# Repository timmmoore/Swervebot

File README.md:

# Swervebot

https://cad.onshape.com/documents/ee819cf6ea491e04f0fba739/w/47ab37900572e080b95199d2/e/a63b98e65827662d9141c87c

https://cad.onshape.com/documents/98357d3c8f8b098add8002f2/w/b5a1efd9deb641ade0f32837/e/772a9ea7ca7ad6a00d48e67d

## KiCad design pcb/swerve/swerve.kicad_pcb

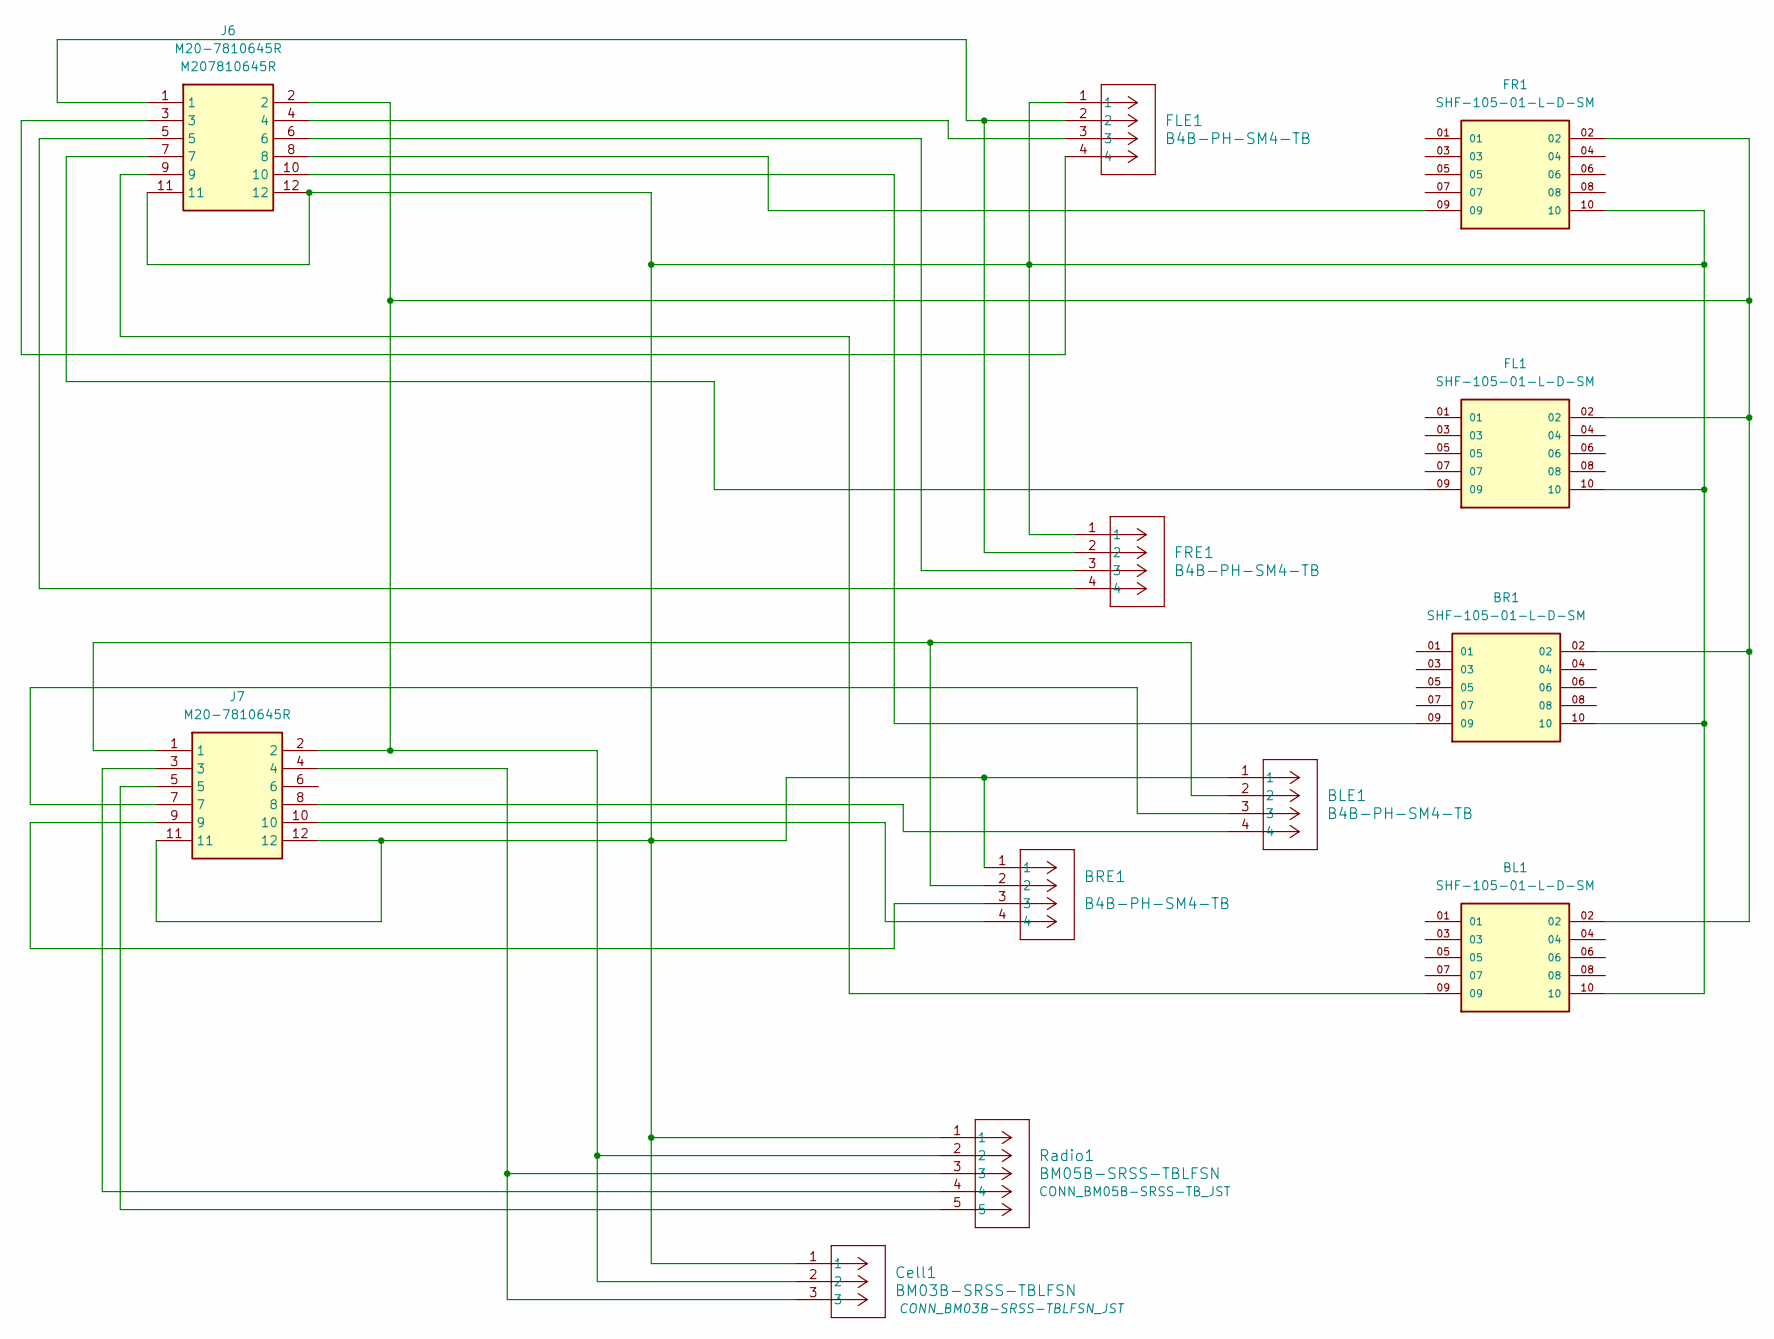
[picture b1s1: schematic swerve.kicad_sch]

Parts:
BL1: SHF-105-01-L-D-SM; SAMTEC_SHF-105-01-L-D-SM; PARTREV A
BLE1: B4B-PH-SM4-TB; JST_PH_B4B-PH-SM4-TB_1x04-1MP_P2.00mm_Vertical
BR1: SHF-105-01-L-D-SM; SAMTEC_SHF-105-01-L-D-SM; PARTREV A
BRE1: B4B-PH-SM4-TB; JST_PH_B4B-PH-SM4-TB_1x04-1MP_P2.00mm_Vertical
Cell1: BM03B-SRSS-TBLFSN; CONN_BM03B-SRSS-TBLFSN_JST
FL1: SHF-105-01-L-D-SM; SAMTEC_SHF-105-01-L-D-SM; PARTREV A
FLE1: B4B-PH-SM4-TB; JST_PH_B4B-PH-SM4-TB_1x04-1MP_P2.00mm_Vertical
FR1: SHF-105-01-L-D-SM; SAMTEC_SHF-105-01-L-D-SM; PARTREV A
FRE1: B4B-PH-SM4-TB; JST_PH_B4B-PH-SM4-TB_1x04-1MP_P2.00mm_Vertical
J6, J7: M20-7810645R; M207810645R; Manufacturer_Part_Number M20-7810645R; Mouser Part Number 855-M20-7810645R
Radio1: BM05B-SRSS-TBLFSN; CONN_BM05B-SRSS-TB_JST

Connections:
unnamed: BL1.02, BR1.02, Cell1.2, FL1.02, FR1.02, J6.2, J7.2, Radio1.2
unnamed: BL1.09, J6.9
unnamed: BL1.10, BLE1.1, BR1.10, BRE1.1, Cell1.1, FL1.10, FLE1.1, FR1.10, FRE1.1, J6.11, J6.12, J7.11, J7.12, Radio1.1
unnamed: BLE1.2, BRE1.2, J7.1
unnamed: BLE1.3, J7.7
unnamed: BLE1.4, J7.8
unnamed: BR1.09, J6.10
unnamed: BRE1.3, J7.9
unnamed: BRE1.4, J7.10
unnamed: Cell1.3, J7.4, Radio1.3
unnamed: FL1.09, J6.7
unnamed: FLE1.2, FRE1.2, J6.1
unnamed: FLE1.3, J6.4
unnamed: FLE1.4, J6.3
unnamed: FR1.09, J6.8
unnamed: FRE1.3, J6.6
unnamed: FRE1.4, J6.5
unnamed: J7.3, Radio1.4
unnamed: J7.5, Radio1.5

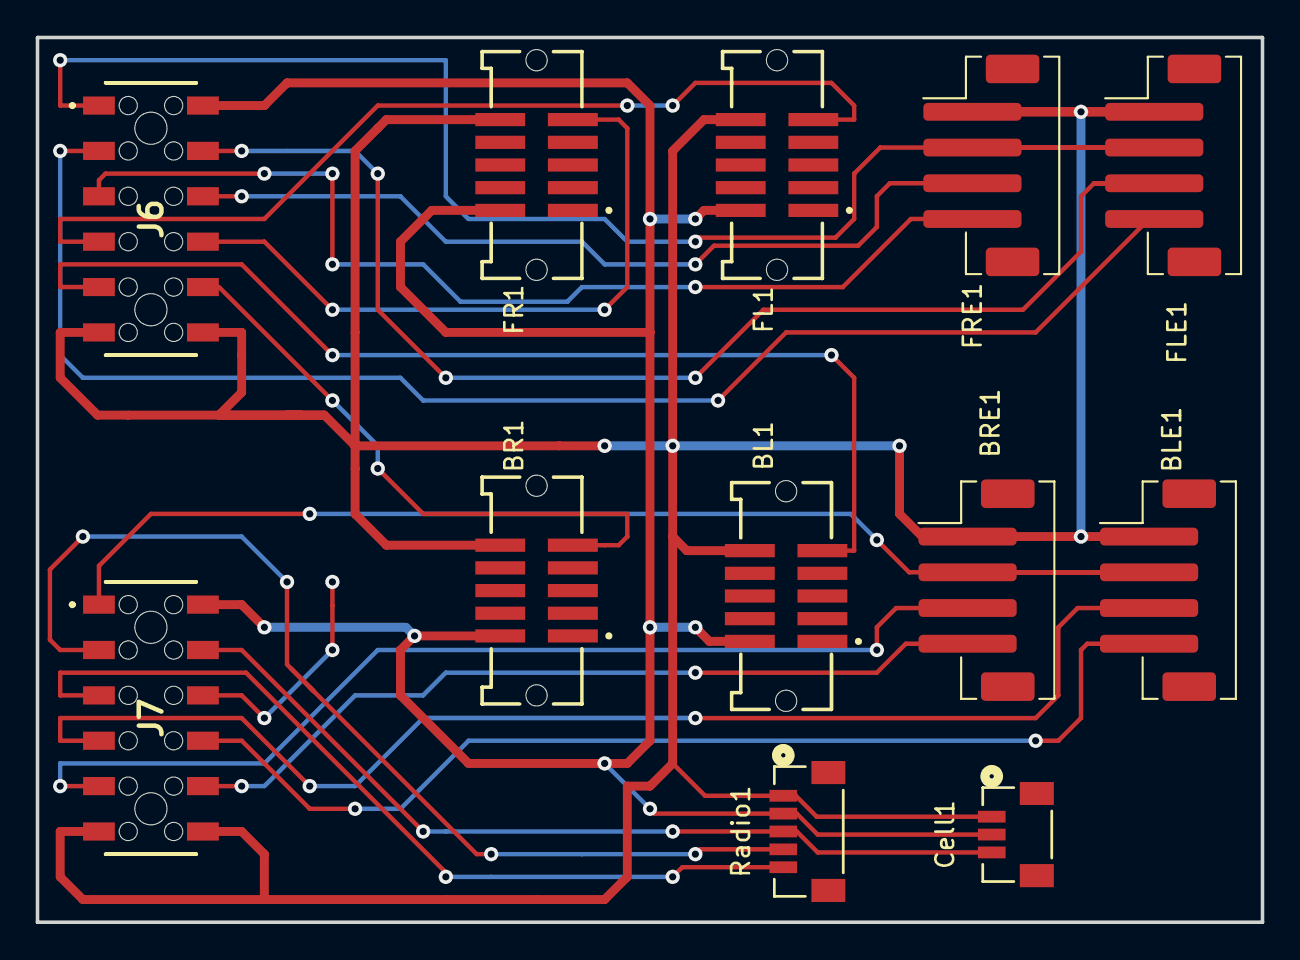
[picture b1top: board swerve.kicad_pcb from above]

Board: 2 copper layers, 68.6 x 49.5 mm, 12 parts (0 on the bottom side), 19 nets.

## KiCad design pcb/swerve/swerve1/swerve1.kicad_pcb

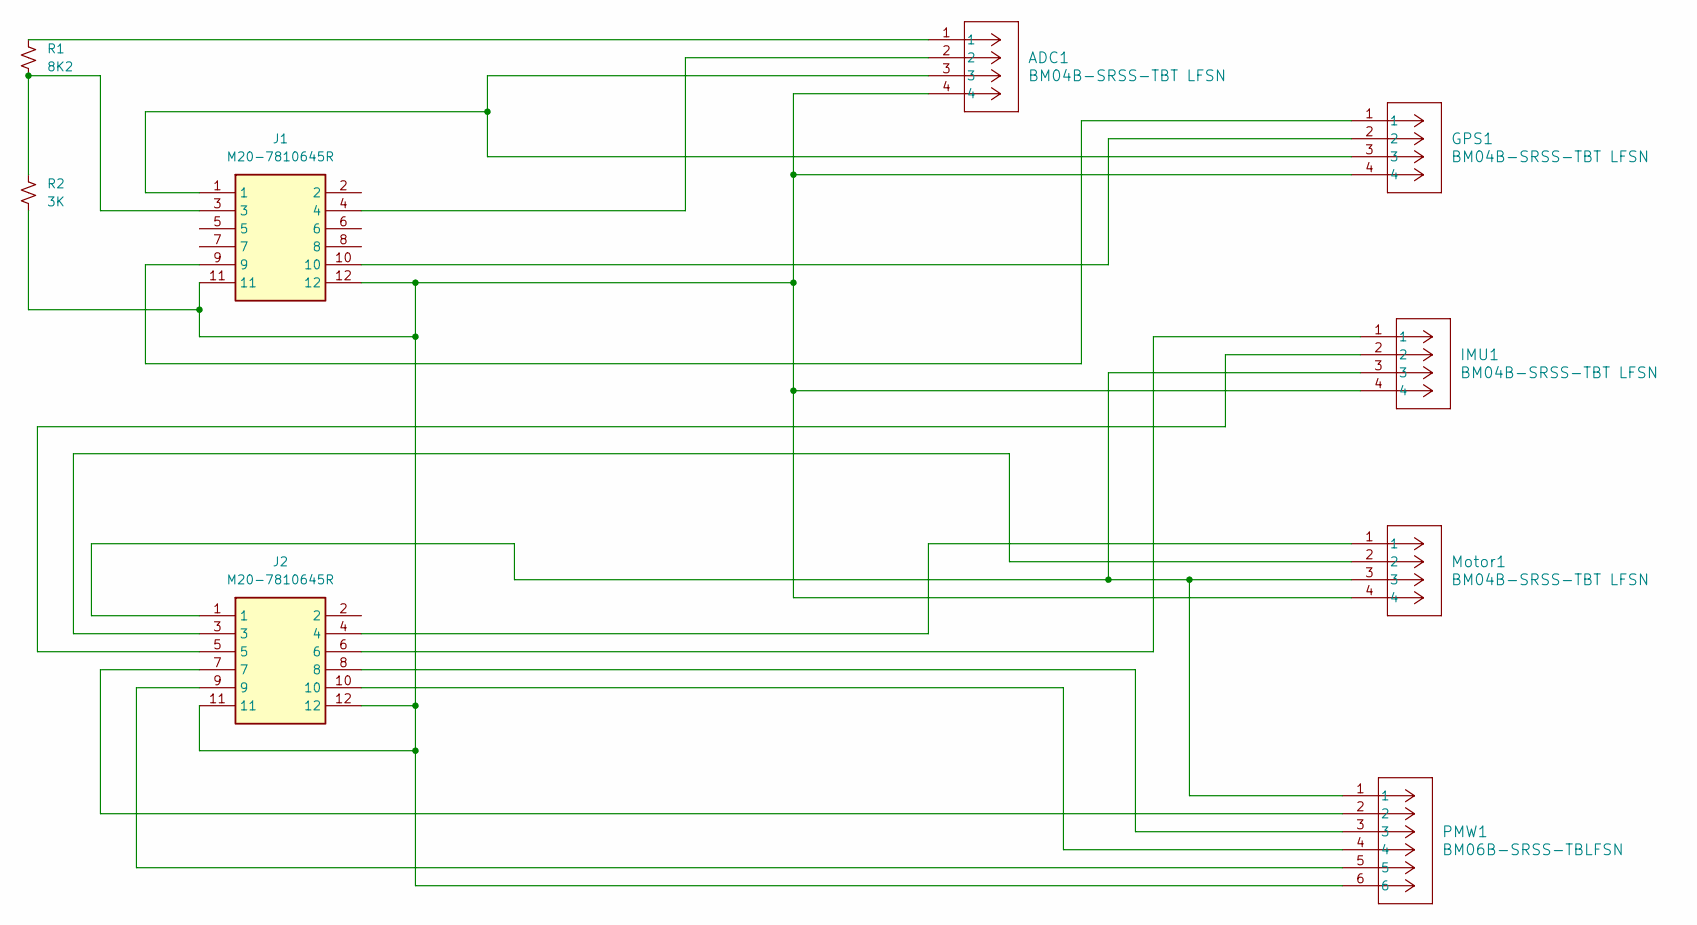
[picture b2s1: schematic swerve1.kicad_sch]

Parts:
ADC1: BM04B-SRSS-TBT LFSN; CONN_BM04B-SRSS-TBT LFSN_JST
GPS1: BM04B-SRSS-TBT LFSN; CONN_BM04B-SRSS-TBT LFSN_JST
IMU1: BM04B-SRSS-TBT LFSN; CONN_BM04B-SRSS-TBT LFSN_JST
J1, J2: M20-7810645R; M207810645R; Manufacturer_Part_Number M20-7810645R; Mouser Part Number 855-M20-7810645R
Motor1: BM04B-SRSS-TBT LFSN; CONN_BM04B-SRSS-TBT LFSN_JST
PMW1: BM06B-SRSS-TBLFSN; CONN_BM06B-SRSS-TB_JST
R1: 8K2; R_0805_2012Metric_Pad1.20x1.40mm_HandSolder
R2: 3K; R_0805_2012Metric_Pad1.20x1.40mm_HandSolder

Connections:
unnamed: ADC1.1, R1.1
unnamed: ADC1.2, J1.4
unnamed: ADC1.3, GPS1.3, J1.1
unnamed: ADC1.4, GPS1.4, IMU1.4, J1.11, J1.12, J2.11, J2.12, Motor1.4, PMW1.6, R2.2
unnamed: GPS1.1, J1.9
unnamed: GPS1.2, J1.10
unnamed: IMU1.1, J2.6
unnamed: IMU1.2, J2.5
unnamed: IMU1.3, J2.1, Motor1.3, PMW1.1
unnamed: J1.3, R1.2, R2.1
unnamed: J2.3, Motor1.2
unnamed: J2.4, Motor1.1
unnamed: J2.7, PMW1.2
unnamed: J2.8, PMW1.3
unnamed: J2.9, PMW1.5
unnamed: J2.10, PMW1.4

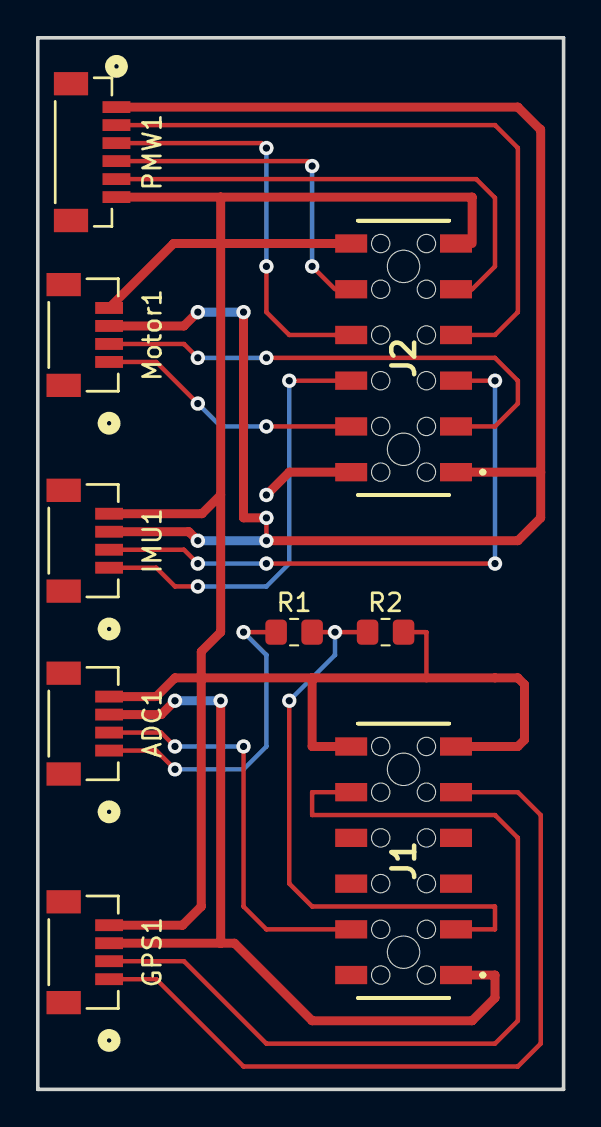
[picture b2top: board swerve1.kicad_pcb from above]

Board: 2 copper layers, 29.2 x 58.4 mm, 9 parts (0 on the bottom side), 16 nets.

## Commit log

2023-06-20 first commit
    First commit
2023-06-20 move test programs to test dir
2023-07-12 new docs
2023-07-13 setting motor direction and pid constants
2023-07-15 more tuning and fixed gps/pmw bugs
2023-07-18 osh version
2023-07-18 fine tuning pids
2023-07-18 photos
2023-07-18 gps debug message
2023-07-18 schematic and render of boards
2023-07-26 update docs
2023-07-26 update pcb
2023-07-26 sport working, quadrature encoder update
2023-07-28 updated pcb
2023-07-28 updated telemetry
2023-07-28 tx16s lua script
2023-07-28 optical flow telemetry
2023-07-28 move test code
2023-07-29 flowx,y working
2023-07-29 drawswerve
2023-07-29 use throttle to limit speed
2023-07-30 updated comments
2023-07-30 updated gps telemetry
2023-07-30 make velocity period configurable
2023-07-30 move to tests
2023-07-30 add encoder speed
2023-07-30 correct wheel position
2023-07-30 battery voltage and barometric telemetry
2023-08-01 updated photos
2023-08-01 comments
2023-08-02 datasheets
2023-08-02 temp telemetry
2023-08-02 fix temp pins
2023-08-02 pcb backup
2023-08-02 minor tidy
2023-08-03 add battery cell telemetry
2023-08-03 speed up i2c bus
2023-08-04 refactor getdata
2023-08-04 doc update
2023-08-04 fix telemetry on motorstop and comments
2023-08-07 wifi programming
2023-08-07 fixed missing debug4
2023-08-07 brake and i2c speed changes
2023-08-07 delay for wfi, comments and debug messages
2023-08-07 i2c bus speed
2023-08-07 ignore .binary file
2023-08-07 p2 edge doc
2023-08-07 voltage telemetry fixes
2023-08-07 proploader flash working
2023-08-07 skipping stopping on min battery if
2023-08-13 flash batch file
2023-08-13 fix temp telemetry
2023-08-13 controlled fan
2023-08-13 debug logical and real pin offsets
2023-08-13 fan test routine
2023-08-13 temp test routine
2023-08-13 controlled motor fan
2023-08-13 battery/temp telemetry, config for motor connection changes
2023-08-13 linefeed changes
2023-08-13 test flash batch
2023-08-13 extra routine
2023-08-13 ignore all binaries and zip files
2023-08-13 denoise temp ADC sensor
2023-08-13 denoise temp sensor, correct battery ratio
2023-08-15 license
2023-08-15 tidy init
2023-08-15 fan on/off and license
2023-08-15 tidy, remove spin init dup
2023-08-15 remove adc test code, rc channel to switch pid update
2023-08-16 angle changes to 0-3600
2023-08-16 null function
2023-08-16 fix float display bug
2023-08-16 led always to bitmask
2023-08-16 comments, maxangle, pid constants
2023-08-16 verbose on
2023-08-16 minor changes and comment updates
2023-08-16 del temp files
2023-08-16 del kicad baclups
2023-08-16 correct pcb directories
2023-08-16 reduce start up delay
2023-08-16 name
2023-08-16 using pcb
2023-08-17 missed inverting 2 drive motors
2023-08-18 update float comparsion test prog
2023-08-29 add images to readme
2023-08-29 comments and set output to high at start
2023-08-30 add bom
2023-09-21 update to use debug
2023-09-21 comment
2023-09-25 add nan tests and updated frel code
2023-09-26 remove frel
2023-09-26 reduce stack
2023-10-07 updated render
2023-10-07 lidar
2023-10-07 debug rather than serial
2023-10-07 nn trainer
2023-10-07 nn utilities
2023-10-07 add lidar and nn
2023-10-07 integration lidar for autoroam
2023-10-09 move battery config to separate file
2023-10-09 enable gps, lidar, etc
2023-10-09 float sdo until used
2023-10-09 new repeat style
2023-10-09 use 8 lidar and x/y/r as input, new weights
2023-10-09 limits on validate temp
2023-10-09 new training and model
2023-10-09 Update swervebot.spin2
    battery to separate file
    temp limits
    sensor loop count
    nn test
2023-10-10 remove serial port
2023-10-10 lidar found
2023-10-10 nn_config
2023-10-10 nn training flag
2023-10-10 lidar fixes
2023-10-17 i2c device for 8 pwm outputs
2023-10-17 remove unused telemetry
2023-10-17 no longer using serial port
2023-10-17 revert spi change
2023-10-17 move unused objects to lib directory
2023-10-17 corrected drive direction, was inverted
2023-10-17 correct add64 for -ve
2023-10-17 change to 3400 clk speed
2023-10-17 removed
2023-10-17 use new motordriver
2023-10-17 increase rotations allowed before delete distance
2023-10-17 driver for i2c pwm device
2023-10-17 attempt to improve wake reliabity
2023-10-17 tidy up
2023-10-18 Correct stopping behavior
2023-10-18 added support for qt-py board
2023-10-18 tidy
2023-10-18 add debug
2023-10-21 fix motor invert
2023-10-21 correct offsets, inverts and pid tuning for new esv
2023-10-21 correct motor stop value
2024-07-04 Create swerve_driver.ino
    new swerve module driver
2024-07-28 i2c scanner for pico
    When electronics is using pico-w
2024-07-28 rp2040 qt py
    Code for rp2040 qt py to control 1 swerve module - motor driver, encoder, angle sensor. Available to main pico-w as a i2c device.
2024-07-29 motor control to uint16 width
2025-04-30 updated to use release xrp board
